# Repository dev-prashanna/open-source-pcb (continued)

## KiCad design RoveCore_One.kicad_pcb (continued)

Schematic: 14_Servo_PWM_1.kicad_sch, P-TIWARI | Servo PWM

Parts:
C60, C61: 100nF 16V; C_0603_1608Metric; MPN GRM188R71C104KA01D
J12: SERVO 1; PinHeader_1x03_P2.54mm_Vertical; MPN 61300311121
J13: SERVO 2; PinHeader_1x03_P2.54mm_Vertical; MPN 61300311121
J14: SERVO 3; PinHeader_1x03_P2.54mm_Vertical; MPN 61300311121
J15: SERVO 4; PinHeader_1x03_P2.54mm_Vertical; MPN 61300311121
R50, R52, R54, R56: 220; R_0603_1608Metric; MPN RC0603FR-07220RL
R51, R53, R55, R57: 100k; R_0603_1608Metric; MPN RC0603FR-07100KL
U19: PCA9685PW,118; TSSOP-28_4.4x9.7mm_P0.65mm; MPN PCA9685PW,118
U20: SN74AHCT1G125DBVR; SOT-23-5_Board; MPN SN74AHCT1G125DBVR

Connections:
+3V3: C60.1, U19.28 (VDD); also elsewhere on the board
BAT5: C61.1, U20.5 (VCC); also elsewhere on the board
GND: C60.2, C61.2, J12.1, J13.1, J14.1, J15.1, R51.2, R53.2, R55.2, R57.2, U19.1 (A0), U19.2 (A1), U19.3 (A2), U19.4 (A3), U19.5 (A4), U19.14 (VSS), U19.24 (A5), U19.25 (EXTCLK), U20.3 (GND); also elsewhere on the board
I2C_SCL: U19.26 (SCL); also elsewhere on the board
I2C_SDA: U19.27 (SDA); also elsewhere on the board
SERVO5: J12.2, J13.2, J14.2, J15.2; also elsewhere on the board
SERVO_OE: U19.23 (~OE), U20.1; also elsewhere on the board
SERVO_OUT0: J12.3, R50.2, R51.1
SERVO_OUT1: J13.3, R52.2, R53.1
SERVO_OUT2: J14.3, R54.2, R55.1
SERVO_OUT3: J15.3, R56.2, R57.1
SERVO_PWM0: U19.6 (LED0); also elsewhere on the board
SERVO_PWM1: U19.7 (LED1); also elsewhere on the board
SERVO_PWM2: U19.8 (LED2); also elsewhere on the board
SERVO_PWM3: U19.9 (LED3), U20.2
SERVO_SIG0: R50.1; also elsewhere on the board
SERVO_SIG1: R52.1; also elsewhere on the board
SERVO_SIG2: R54.1; also elsewhere on the board
SERVO_SIG3: R56.1, U20.4

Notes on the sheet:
PCA9685 0x40; default all-call 0x70, disable if conflicting extension is installed. GPIO15 high disables AHCT output buffers and PCA9685. Set low only after setting valid 50Hz pulses. Each servo: GND / servo rail / 5V PWM. Servo supply and BAT5 logic are distinct. Unused PWM channels intentionally 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

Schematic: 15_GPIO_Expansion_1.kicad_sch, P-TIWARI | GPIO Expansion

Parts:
C62: 100nF 16V; C_0603_1608Metric; MPN GRM188R71C104KA01D
J16: I2C 3V3; JST_GH_SM04B-GHS-TB_1x04-1MP_P1.25mm_Horizontal; MPN SM04B-GHS-TB(LF)(SN)
J17: SPI / LORA; JST_GH_SM06B-GHS-TB_1x06-1MP_P1.25mm_Horizontal; MPN SM06B-GHS-TB(LF)(SN)
J18: GPS / UART; JST_GH_SM04B-GHS-TB_1x04-1MP_P1.25mm_Horizontal; MPN SM04B-GHS-TB(LF)(SN)
J19: GPIO EXP 3V3; PinHeader_1x10_P2.00mm_Vertical; MPN M22-2011005
J20: ESP GPIO SHARED; PinHeader_1x10_P2.00mm_Vertical; MPN M22-2011005
J21: ESP GPIO INPUTS; PinHeader_1x08_P2.00mm_Vertical; MPN M22-2010805
TP1: EXP_B0; ServicePad_0.5mm; MPN PCB copper feature
TP2: EXP_B1; ServicePad_0.5mm; MPN PCB copper feature
TP3: EXP_B2; ServicePad_0.5mm; MPN PCB copper feature
U21: MCP23017-E/SS; SSOP-28_5.3x10.2mm_P0.65mm; MPN MCP23017-E/SS

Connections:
+3V3: C62.1, J16.1, J17.2, J18.2, J19.2, J20.2, U21.9 (V_{DD}); also elsewhere on the board
BAT_ADC: J20.8; also elsewhere on the board
BUZZ_PWM: J21.3; also elsewhere on the board
EN: U21.18 (~RESET); also elsewhere on the board
ENC_LA: J21.4; also elsewhere on the board
ENC_LB: J21.5; also elsewhere on the board
ENC_RA: J21.6; also elsewhere on the board
ENC_RB: J21.7; also elsewhere on the board
EXP_B0: TP1.1, U21.1 (GPB0)
EXP_B1: TP2.1, U21.2 (GPB1)
EXP_B2: TP3.1, U21.3 (GPB2)
EXP_B3: J19.6, U21.4 (GPB3)
EXP_B4: J19.7, U21.5 (GPB4)
EXP_B5: J19.8, U21.6 (GPB5)
EXP_B6: J19.9, U21.7 (GPB6)
EXP_B7: J19.10, U21.8 (GPB7); also elsewhere on the board
GND: C62.2, J16.2, J17.1, J18.1, J19.1, J19.3, J19.4, J19.5, J20.1, J21.1, U21.10 (V_{SS}), U21.15 (A0), U21.16 (A1), U21.17 (A2); also elsewhere on the board
I2C_SCL: J16.4, U21.12 (SCK); also elsewhere on the board
I2C_SDA: J16.3, U21.13 (SDA); also elsewhere on the board
IMU_INT: J20.7; also elsewhere on the board
M_A1: J20.3; also elsewhere on the board
M_A2: J20.4; also elsewhere on the board
M_B1: J20.5; also elsewhere on the board
M_B2: J20.6; also elsewhere on the board
M_FAULT: U21.22 (GPA1); also elsewhere on the board
M_SLEEP: U21.21 (GPA0); also elsewhere on the board
RGB_B: U21.28 (GPA7); also elsewhere on the board
RGB_G: U21.27 (GPA6); also elsewhere on the board
RGB_R: U21.26 (GPA5); also elsewhere on the board
SERVO_OE: J21.2; also elsewhere on the board
SPI_CS: J17.6, J21.8; also elsewhere on the board
SPI_MISO: J17.5; also elsewhere on the board
SPI_MOSI: J17.4; also elsewhere on the board
SPI_SCK: J17.3; also elsewhere on the board
TOF_INT: U21.24 (GPA3); also elsewhere on the board
TOF_XSHUT: U21.23 (GPA2); also elsewhere on the board
UART_RX: J18.4; also elsewhere on the board
UART_TX: J18.3; also elsewhere on the board
USER_BTN: U21.25 (GPA4); also elsewhere on the board
US_ECHO: J20.10; also elsewhere on the board
US_TRIG: J20.9; also elsewhere on the board

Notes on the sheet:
MCP23017 fixed 0x20. GPA0 sleep defaults LOW by external resistor; all pins reset as inputs. GPA2 must be open-drain emulated: output LOW for shutdown, input for release; never drive HIGH. GPB0..7 expansion are 3V3 GPIO; GPB7 also drives onboard load MOSFET. GPIO headers expose SHARED nets: disable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

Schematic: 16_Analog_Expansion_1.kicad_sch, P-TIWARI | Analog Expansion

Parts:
C63: 100nF 16V; C_0603_1608Metric; MPN GRM188R71C104KA01D
C64, C65, C66, C67: 10nF 25V; C_0603_1608Metric; MPN GRM188R71E103KA01D
D10, D11, D12, D13: BAT54S; SOT-23; MPN BAT54S-7-F
J22: ANALOG 0-3V3; JST_GH_SM06B-GHS-TB_1x06-1MP_P1.25mm_Horizontal; MPN SM06B-GHS-TB(LF)(SN)
R58, R59, R60, R61: 4.7k; R_0603_1608Metric; MPN RC0603FR-074K7L
U22: ADS1115IDGSR; TSSOP-10_3x3mm_P0.5mm; MPN ADS1115IDGSR

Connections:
+3V3: J22.1; also elsewhere on the board
+3V3_SENS: C63.1, D10.2 (K), D11.2 (K), D12.2 (K), D13.2 (K), U22.8 (VDD); also elsewhere on the board
AN0: C64.1, D10.3 (COM), R58.2, U22.4 (AIN0)
AN1: C65.1, D11.3 (COM), R59.2, U22.5 (AIN1)
AN2: C66.1, D12.3 (COM), R60.2, U22.6 (AIN2)
AN3: C67.1, D13.3 (COM), R61.2, U22.7 (AIN3)
AN_IN0: J22.3, R58.1
AN_IN1: J22.4, R59.1
AN_IN2: J22.5, R60.1
AN_IN3: J22.6, R61.1
GND: C63.2, C64.2, C65.2, C66.2, C67.2, D10.1 (A), D11.1 (A), D12.1 (A), D13.1 (A), J22.2, U22.1 (ADDR), U22.3 (GND); also elsewhere on the board
I2C_SCL: U22.10 (SCL); also elsewhere on the board
I2C_SDA: U22.9 (SDA); also elsewhere on the board

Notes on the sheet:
ADS1115 address 0x48, 860 samples/s aggregate maximum. Choose PGA +/-4.096V. Input voltage range remains 0..3.3V; PGA range is NOT input tolerance. 4.7k / 10nF filtering with Schottky clamps. Suitable for analog line sensor array. 4 channels sequentially sampled; high-speed line control may need an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

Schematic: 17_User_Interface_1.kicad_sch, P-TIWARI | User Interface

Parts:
BZ1: PKLCS1212E4001-R1; Buzzer_Murata_PKLCS1212E; MPN PKLCS1212E4001-R1
C68: 100nF 16V; C_0603_1608Metric; MPN GRM188R71C104KA01D
D4, D6: GREEN; LED_0603_1608Metric; MPN LTST-C190KGKT
D5: RED; LED_0603_1608Metric; MPN LTST-C190KRKT
D7: BLUE; LED_0603_1608Metric; MPN LTST-C193TBKT-5A
D8: SS34; D_SMA; MPN SS34
Q6, Q7: AO3400A; SOT-23; MPN AO3400A
R62: 10k; R_0603_1608Metric; MPN RC0603FR-0710KL
R63, R64, R65, R66, R69: 1k; R_0603_1608Metric; MPN RC0603FR-071KL
R67, R70: 100; R_0603_1608Metric; MPN RC0603FR-07100RL
R68, R71: 100k; R_0603_1608Metric; MPN RC0603FR-07100KL
SW3: SW3; SW_Push_1P1T-SH_NO_CK_KMR2xxG; MPN KMR221GLFS

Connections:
+3V3: BZ1.1 (+), R62.1, R63.1, R64.1, R65.1, R66.1, R69.1; also elsewhere on the board
BAT5: D8.1 (K); also elsewhere on the board
BUZZ_GATE: Q6.1 (G), R67.2, R68.1
BUZZ_LOW: BZ1.2 (-), Q6.3 (D), R69.2
BUZZ_PWM: R67.1; also elsewhere on the board
EXP_B7: R70.1; also elsewhere on the board
GND: C68.2, D4.1 (K), Q6.2 (S), Q7.2 (S), R68.2, R71.2, SW3.2; also elsewhere on the board
LED_B: D7.2 (A), R66.2
LED_G: D6.2 (A), R65.2
LED_R: D5.2 (A), R64.2
LOAD_GATE: Q7.1 (G), R70.2, R71.1
LOAD_LOW: D8.2 (A), Q7.3 (D); also elsewhere on the board
POWER_LED: D4.2 (A), R63.2
RGB_B: D7.1 (K); also elsewhere on the board
RGB_G: D6.1 (K); also elsewhere on the board
RGB_R: D5.1 (K); also elsewhere on the board
USER_BTN: C68.1, R62.2, SW3.1; also elsewhere on the board

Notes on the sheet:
R/G/B discrete programmable LEDs on expander GPA5..7; use green for Wi-Fi status. Piezo buzzer via GPIO2 MOSFET and discharge resistor. User button active LOW on GPA4. GPB7 load output 5V/250mA max, diode-protected for small inductive loads. BAT5 accessory budget shared. CAN: external 3V3 transceiv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

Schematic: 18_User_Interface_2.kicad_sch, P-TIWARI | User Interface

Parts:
J23: LOAD 5V 0.25A; JST_GH_SM02B-GHS-TB_1x02-1MP_P1.25mm_Horizontal; MPN SM02B-GHS-TB(LF)(SN)

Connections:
BAT5: J23.1; also elsewhere on the board
LOAD_LOW: J23.2; also elsewhere on the board

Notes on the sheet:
R/G/B discrete programmable LEDs on expander GPA5..7; use green for Wi-Fi status. Piezo buzzer via GPIO2 MOSFET and discharge resistor. User button active LOW on GPA4. GPB7 load output 5V/250mA max, diode-protected for small inductive loads. BAT5 accessory budget shared. CAN: external 3V3 transceiv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

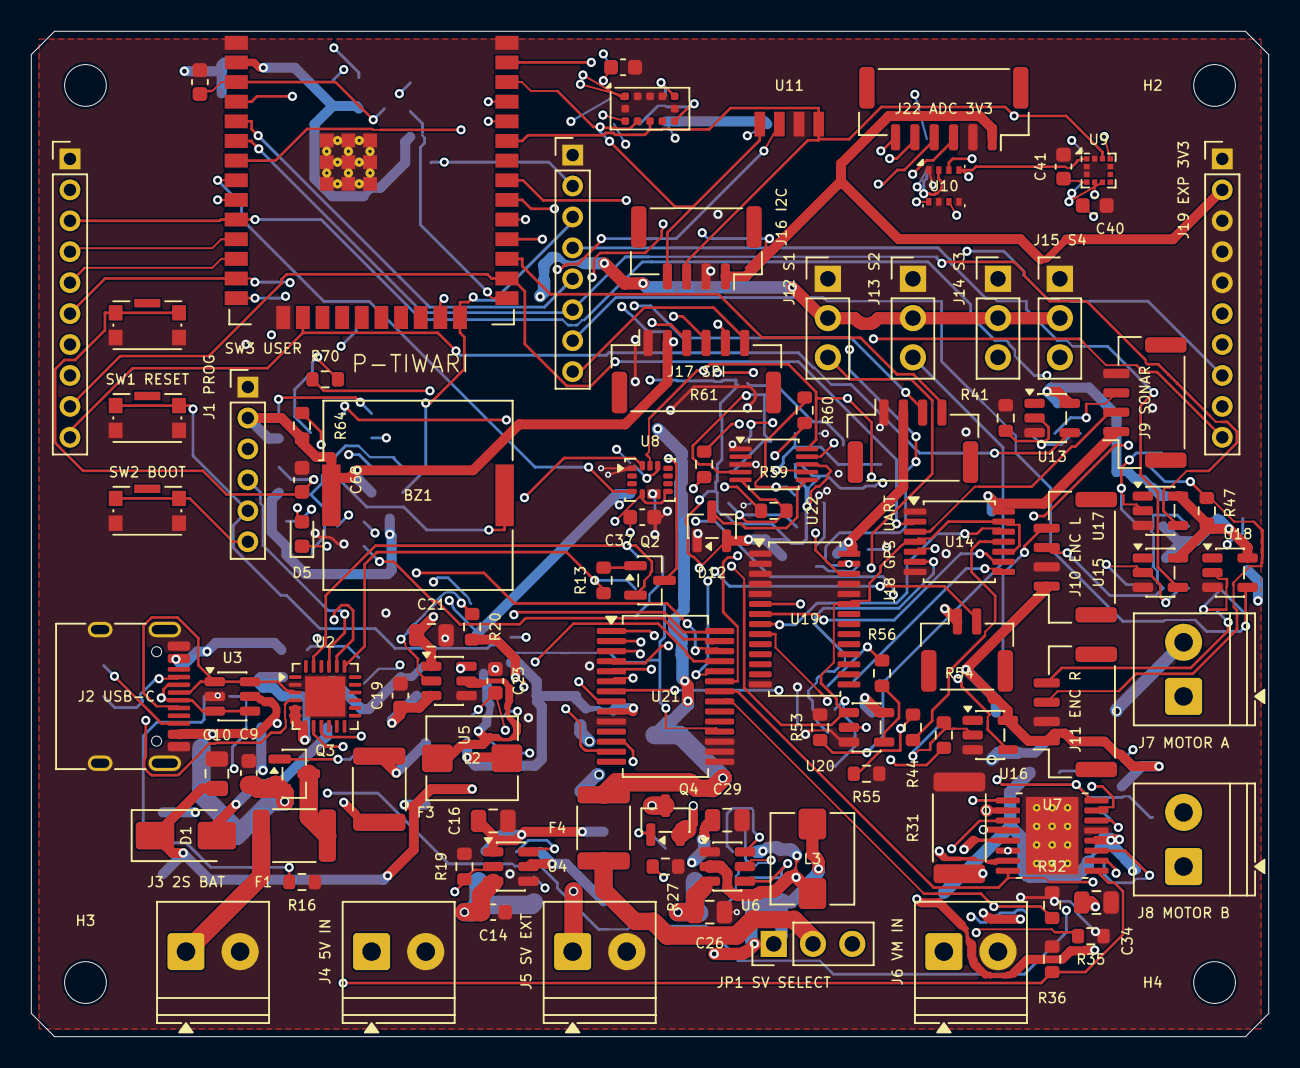
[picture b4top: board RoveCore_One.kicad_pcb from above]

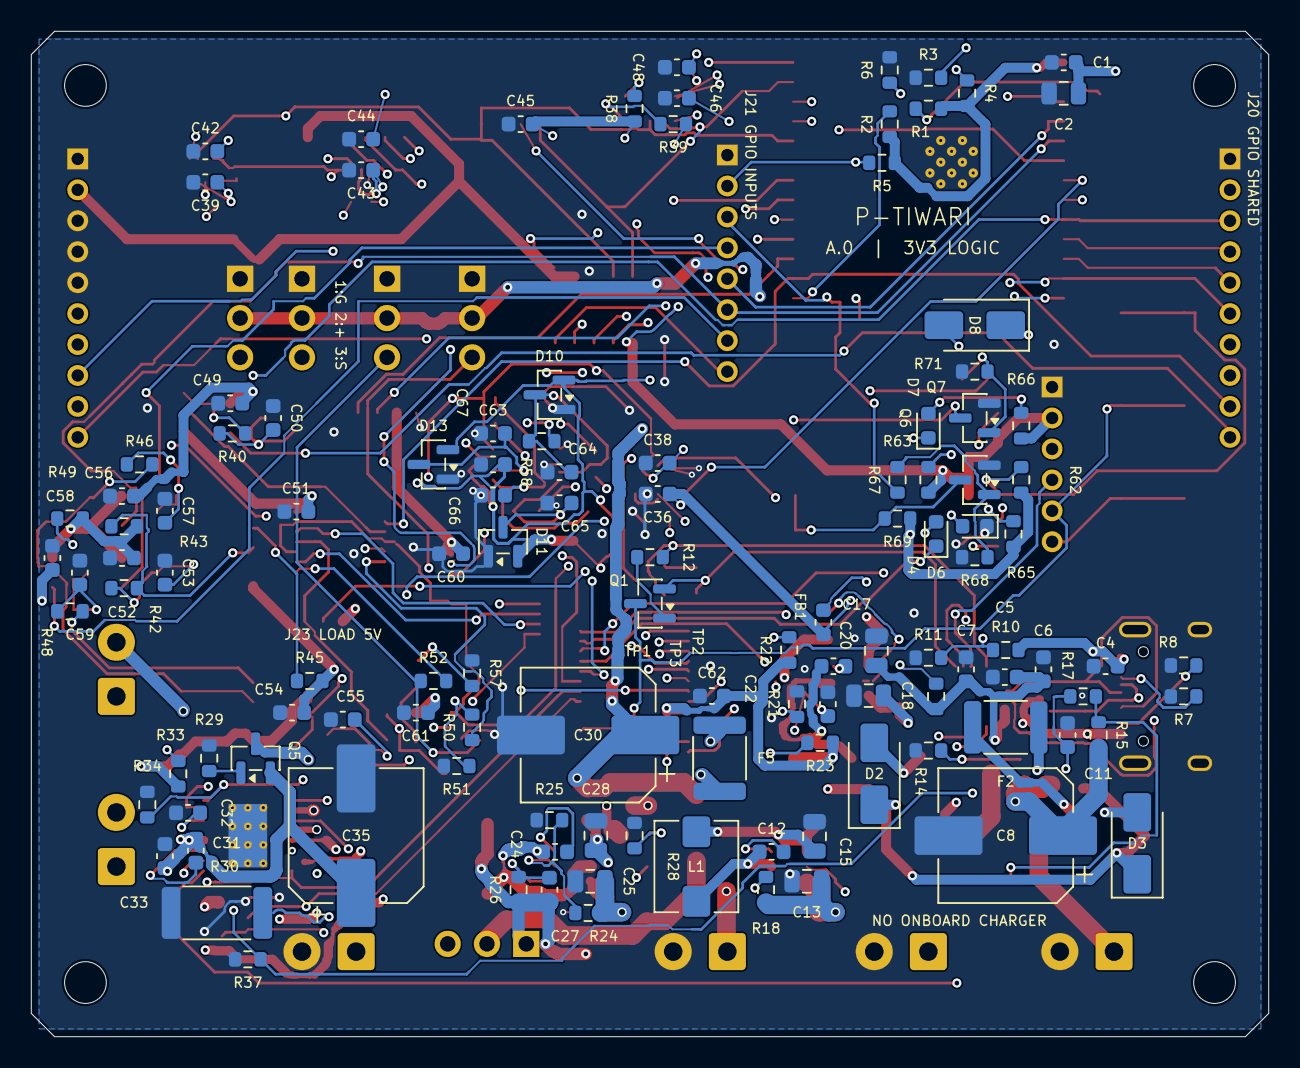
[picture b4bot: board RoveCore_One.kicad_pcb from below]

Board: 4 copper layers, 80.0 x 65.0 mm, 224 parts (122 on the bottom side), 135 nets.

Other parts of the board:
H1, H2, H3, H4: MountingHole_2.7mm_M2.5

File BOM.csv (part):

Reference,Value,MPN,Manufacturer,Footprint,Section,Datasheet
U1,ESP32-WROOM-32E-N8,ESP32-WROOM-32E-N8,Espressif,RoveCore:ESP32-WROOM-32E_Board,Controller,https://documentation.espressif.com/esp32-wroom-32e_esp32-wr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
C1,100nF 16V,GRM188R71C104KA01D,Murata,Capacitor_SMD:C_0603_1608Metric,Controller,
C2,22uF 10V,GRM21BR61A226ME44L,Murata,Capacitor_SMD:C_0805_2012Metric,Controller,
R1,10k,RC0603FR-0710KL,Yageo,Resistor_SMD:R_0603_1608Metric,Controller,
C3,1uF 16V,GRM188R61C105KA12D,Murata,Capacitor_SMD:C_0603_1608Metric,Controller,
R2,10k,RC0603FR-0710KL,Yageo,Resistor_SMD:R_0603_1608Metric,Controller,
R3,10k,RC0603FR-0710KL,Yageo,Resistor_SMD:R_0603_1608Metric,Controller,
R4,10k,RC0603FR-0710KL,Yageo,Resistor_SMD:R_0603_1608Metric,Controller,
R5,10k,RC0603FR-0710KL,Yageo,Resistor_SMD:R_0603_1608Metric,Controller,
R6,100k,RC0603FR-07100KL,Yageo,Resistor_SMD:R_0603_1608Metric,Controller,
SW1,SW1,KMR221GLFS,C&K,Button_Switch_SMD:SW_Push_1P1T-SH_NO_CK_KMR2xxG,Controller,
SW2,SW2,KMR221GLFS,C&K,Button_Switch_SMD:SW_Push_1P1T-SH_NO_CK_KMR2xxG,Controller,
J1,SERVICE 3V3,M22-2010605,Harwin,Connector_PinHeader_2.00mm:PinHeader_1x06_P2.00mm_Vertical,Controller,
J2,USB-C 5V DATA,TYPE-C-31-M-12,HRO,Connector_USB:USB_C_Receptacle_HRO_TYPE-C-31-M-12,USB Programming,
R7,5.1k,RC0603FR-075K1L,Yageo,Resistor_SMD:R_0603_1608Metric,USB Programming,
R8,5.1k,RC0603FR-075K1L,Yageo,Resistor_SMD:R_0603_1608Metric,USB Programming,
C4,1uF 16V,GRM188R61C105KA12D,Murata,Capacitor_SMD:C_0603_1608Metric,USB Programming,
U2,CP2102N-A02-GQFN24,CP2102N-A02-GQFN24,Silicon Labs,Package_DFN_QFN:QFN-24-1EP_4x4mm_P0.5mm_EP2.6x2.6mm,USB Programming,https://www.silabs.com/documents/public/data-sheets/cp2102n-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
C5,100nF 16V,GRM188R71C104KA01D,Murata,Capacitor_SMD:C_0603_1608Metric,USB Programming,
C6,100nF 16V,GRM188R71C104KA01D,Murata,Capacitor_SMD:C_0603_1608Metric,USB Programming,
C7,4.7uF 10V,GRM188R61A475KE15D,Murata,Capacitor_SMD:C_0603_1608Metric,USB Programming,
R9,1k,RC0603FR-071KL,Yageo,Resistor_SMD:R_0603_1608Metric,USB Programming,
R10,22.1k,RC0603FR-0722K1L,Yageo,Resistor_SMD:R_0603_1608Metric,USB Programming,
R11,47.5k,RC0603FR-0747K5L,Yageo,Resistor_SMD:R_0603_1608Metric,USB Programming,
U3,USBLC6-2SC6,USBLC6-2SC6,STMicroelectronics,Package_TO_SOT_SMD:SOT-23-6,USB Programming,
Q1,MMBT3904,MMBT3904,onsemi,Package_TO_SOT_SMD:SOT-23,USB Programming,
R12,10k,RC0603FR-0710KL,Yageo,Resistor_SMD:R_0603_1608Metric,USB Programming,
Q2,MMBT3904,MMBT3904,onsemi,Package_TO_SOT_SMD:SOT-23,USB Programming,
R13,10k,RC0603FR-0710KL,Yageo,Resistor_SMD:R_0603_1608Metric,USB Programming,
J3,2S BAT 6.4-8.4V,1984617,Phoenix Contact,"TerminalBlock_Phoenix:TerminalBlock_Phoenix_PT-1,5-2-3.5-H_1x02_P3.50mm_Horizontal",Power Inputs,
F1,2A hold,1812L200/16DR,Littelfuse,Fuse:Fuse_1812_4532Metric,Power Inputs,
Q3,AO3401A,AO3401A,Alpha & Omega Semiconductor,Package_TO_SOT_SMD:SOT-23,Power Inputs,https://www.aosmd.com/sites/default/files/res/datasheets/AO3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
R14,100k,RC0603FR-07100KL,Yageo,Resistor_SMD:R_0603_1608Metric,Power Inputs,
C8,470uF 16V,EEE-FK1C471P,Panasonic,Capacitor_SMD:CP_Elec_8x10.5,Power Inputs,
C9,100nF 16V,GRM188R71C104KA01D,Murata,Capacitor_SMD:C_0603_1608Metric,Power Inputs,
J4,EXT 5V LOGIC,1984617,Phoenix Contact,"TerminalBlock_Phoenix:TerminalBlock_Phoenix_PT-1,5-2-3.5-H_1x02_P3.50mm_Horizontal",Power Inputs,
F2,1.1A hold,1812L110/16DR,Littelfuse,Fuse:Fuse_1812_4532Metric,Power Inputs,
F3,0.5A hold,1812L050/24DR,Littelfuse,Fuse:Fuse_1812_4532Metric,Power Inputs,
D1,SS34,SS34,Diodes Inc.,Diode_SMD:D_SMA,Power Inputs,
D2,SS34,SS34,Diodes Inc.,Diode_SMD:D_SMA,Power Inputs,
D3,SS34,SS34,Diodes Inc.,Diode_SMD:D_SMA,Power Inputs,
C10,22uF 10V,GRM21BR61A226ME44L,Murata,Capacitor_SMD:C_0805_2012Metric,Power Inputs,
R15,100k,RC0603FR-07100KL,Yageo,Resistor_SMD:R_0603_1608Metric,Power Inputs,
R16,33k,RC0603FR-0733KL,Yageo,Resistor_SMD:R_0603_1608Metric,Power Inputs,
R17,1k,RC0603FR-071KL,Yageo,Resistor_SMD:R_0603_1608Metric,Power Inputs,
C11,100nF 16V,GRM188R71C104KA01D,Murata,Capacitor_SMD:C_0603_1608Metric,Power Inputs,
U4,AP63205WU-7,AP63205WU-7,Diodes Inc.,Package_TO_SOT_SMD:TSOT-23-6,Logic Regulators,https://www.diodes.com/datasheet/download/AP63200-AP63201-AP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
R18,100k,RC0603FR-07100KL,Yageo,Resistor_SMD:R_0603_1608Metric,Logic Regulators,
R19,27.4k,RC0603FR-0727K4L,Yageo,Resistor_SMD:R_0603_1608Metric,Logic Regulators,
C12,100nF 16V,GRM188R71C104KA01D,Murata,Capacitor_SMD:C_0603_1608Metric,Logic Regulators,
C13,10uF 16V,GRM21BR61C106KE15L,Murata,Capacitor_SMD:C_0805_2012Metric,Logic Regulators,
C14,100nF 16V,GRM188R71C104KA01D,Murata,Capacitor_SMD:C_0603_1608Metric,Logic Regulators,
L1,4.7uH,SRP5030T-4R7M,Bourns,Inductor_SMD:L_Bourns_SRP5030T,Logic Regulators,
C15,22uF 10V,GRM21BR61A226ME44L,Murata,Capacitor_SMD:C_0805_2012Metric,Logic Regulators,
C16,22uF 10V,GRM21BR61A226ME44L,Murata,Capacitor_SMD:C_0805_2012Metric,Logic Regulators,
U5,AP63203WU-7,AP63203WU-7,Diodes Inc.,Package_TO_SOT_SMD:TSOT-23-6,Logic Regulators,https://www.diodes.com/datasheet/download/AP63200-AP63201-AP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
R20,100k,RC0603FR-07100KL,Yageo,Resistor_SMD:R_0603_1608Metric,Logic Regulators,
R21,100k,RC0603FR-07100KL,Yageo,Resistor_SMD:R_0603_1608Metric,Logic Regulators,
C17,100nF 16V,GRM188R71C104KA01D,Murata,Capacitor_SMD:C_0603_1608Metric,Logic Regulators,
C18,10uF 16V,GRM21BR61C106KE15L,Murata,Capacitor_SMD:C_0805_2012Metric,Logic Regulators,
C19,100nF 16V,GRM188R71C104KA01D,Murata,Capacitor_SMD:C_0603_1608Metric,Logic Regulators,
L2,4.7uH,SRP5030T-4R7M,Bourns,Inductor_SMD:L_Bourns_SRP5030T,Logic Regulators,
C20,22uF 10V,GRM21BR61A226ME44L,Murata,Capacitor_SMD:C_0805_2012Metric,Logic Regulators,
C21,22uF 10V,GRM21BR61A226ME44L,Murata,Capacitor_SMD:C_0805_2012Metric,Logic Regulators,
FB1,600R @100MHz,BLM18AG601SN1D,Murata,Inductor_SMD:L_0603_1608Metric,Logic Regulators,
C22,4.7uF 10V,GRM188R61A475KE15D,Murata,Capacitor_SMD:C_0603_1608Metric,Logic Regulators,
C23,100nF 16V,GRM188R71C104KA01D,Murata,Capacitor_SMD:C_0603_1608Metric,Logic Regulators,
R22,2.2k,RC0603FR-072K2L,Yageo,Resistor_SMD:R_0603_1608Metric,Logic Regulators,
R23,2.2k,RC0603FR-072K2L,Yageo,Resistor_SMD:R_0603_1608Metric,Logic Regulators,
U6,TPS54302DDCR,TPS54302DDCR,Texas Instruments,Package_TO_SOT_SMD:SOT-23-6,Servo Power,https://www.ti.com/lit/ds/symlink/tps54302.pdf
R24,100k,RC0603FR-07100KL,Yageo,Resistor_SMD:R_0603_1608Metric,Servo Power,
R25,27.4k,RC0603FR-0727K4L,Yageo,Resistor_SMD:R_0603_1608Metric,Servo Power,
C24,100nF 16V,GRM188R71C104KA01D,Murata,Capacitor_SMD:C_0603_1608Metric,Servo Power,
C25,10uF 16V,GRM21BR61C106KE15L,Murata,Capacitor_SMD:C_0805_2012Metric,Servo Power,
C26,10uF 16V,GRM21BR61C106KE15L,Murata,Capacitor_SMD:C_0805_2012Metric,Servo Power,
L3,10uH,SRP5030T-100M,Bourns,Inductor_SMD:L_Bourns_SRP5030T,Servo Power,
R26,100k,RC0603FR-07100KL,Yageo,Resistor_SMD:R_0603_1608Metric,Servo Power,
R27,13.3k,RC0603FR-0713K3L,Yageo,Resistor_SMD:R_0603_1608Metric,Servo Power,
C27,75pF 50V,GRM1885C1H750JA01D,Murata,Capacitor_SMD:C_0603_1608Metric,Servo Power,
C28,22uF 10V,GRM21BR61A226ME44L,Murata,Capacitor_SMD:C_0805_2012Metric,Servo Power,
C29,22uF 10V,GRM21BR61A226ME44L,Murata,Capacitor_SMD:C_0805_2012Metric,Servo Power,
J5,SERVO EXT 5-6V,1984617,Phoenix Contact,"TerminalBlock_Phoenix:TerminalBlock_Phoenix_PT-1,5-2-3.5-H_1x02_P3.50mm_Horizontal",Servo Power,
Q4,AO3401A,AO3401A,Alpha & Omega Semiconductor,Package_TO_SOT_SMD:SOT-23,Servo Power,https://www.aosmd.com/sites/default/files/res/datasheets/AO3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
R28,100k,RC0603FR-07100KL,Yageo,Resistor_SMD:R_0603_1608Metric,Servo Power,
JP1,SERVO SELECT 1-2 BAT / 2-3 EXT,61300311121,Wurth Elektronik,Connector_PinHeader_2.54mm:PinHeader_1x03_P2.54mm_Vertical,Servo Power,
F4,2A hold,1812L200/16DR,Littelfuse,Fuse:Fuse_1812_4532Metric,Servo Power,
C30,470uF 16V,EEE-FK1C471P,Panasonic,Capacitor_SMD:CP_Elec_8x10.5,Servo Power,
J6,VM 3-8.4V,1984617,Phoenix Contact,"TerminalBlock_Phoenix:TerminalBlock_Phoenix_PT-1,5-2-3.5-H_1x02_P3.50mm_Horizontal",Motor Driver,
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
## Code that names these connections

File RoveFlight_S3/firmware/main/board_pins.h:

// Generated from verified GPIO_Allocation.csv. RF-S3-A0 / N8R2 only.
#pragma once
#define PIN_BOOT 0
#define PIN_CURRENT_ADC 1
#define PIN_BAT_ADC 2
#define PIN_PWM_M1 4
#define PIN_PWM_M2 5
#define PIN_PWM_M3 6
#define PIN_PWM_M4 7
#define PIN_I2C_SDA 8
#define PIN_IMU_INT 9
#define PIN_IMU_CS 10
#define PIN_SPI_MOSI 11
#define PIN_SPI_SCK 12
#define PIN_SPI_MISO 13
#define PIN_BARO_CS 14
#define PIN_IR_RX 15
#define PIN_TOF_INT 16
#define PIN_TOF_XSHUT 17
#define PIN_I2C_SCL 18
#define PIN_USB_DM 19
#define PIN_USB_DP 20
#define PIN_STATUS_LED 21
#define PIN_ARM_CLK 38
#define PIN_WD_HEARTBEAT 39
#define PIN_KILL_OD 40
#define PIN_RC_RX 41
#define PIN_RC_TX 42
#define PIN_DEBUG_TX 43
#define PIN_DEBUG_RX 44
#define PIN_FLOW_CS 47
#define PIN_FLOW_INT 48

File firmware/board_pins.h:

// P-TIWARI A.0; pin contract only, not validated application firmware.
#pragma once
namespace p_tiwari {
constexpr int PIN_BOOT = 0;
constexpr int PIN_U0_TX = 1;
constexpr int PIN_BUZZ_PWM = 2;
constexpr int PIN_U0_RX = 3;
constexpr int PIN_US_TRIG = 4;
constexpr int PIN_SPI_CS = 5;
constexpr int PIN_STRAP12 = 12;
constexpr int PIN_US_ECHO = 13;
constexpr int PIN_M_B2 = 14;
constexpr int PIN_SERVO_OE = 15;
constexpr int PIN_UART_RX = 16;
constexpr int PIN_UART_TX = 17;
constexpr int PIN_SPI_SCK = 18;
constexpr int PIN_SPI_MISO = 19;
constexpr int PIN_I2C_SDA = 21;
constexpr int PIN_I2C_SCL = 22;
constexpr int PIN_SPI_MOSI = 23;
constexpr int PIN_M_A1 = 25;
constexpr int PIN_M_A2 = 26;
constexpr int PIN_M_B1 = 27;
constexpr int PIN_IMU_INT = 32;
constexpr int PIN_BAT_ADC = 33;
constexpr int PIN_ENC_RA = 34;
constexpr int PIN_ENC_RB = 35;
constexpr int PIN_ENC_LA = 36;
constexpr int PIN_ENC_LB = 39;
constexpr unsigned IMU_ADDR=0x6A, MAG_ADDR=0x1C, BME_ADDR=0x76, ALS_ADDR=0x10;
constexpr unsigned TOF_ADDR=0x29, PWM_ADDR=0x40, EXP_ADDR=0x20, ADC_ADDR=0x48;
}

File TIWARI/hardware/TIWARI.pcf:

# Physical SG48 pin numbers; generated pin parity is checked against design.json.
set_io clk_12m 35
set_io reset_n 10
set_io uart_rx 9
set_io uart_tx 6
set_io user_led 11
set_io fault_led 12
set_io pwm[0] 13
set_io pwm[1] 18
set_io gpio[0] 2
set_io gpio[1] 3
set_io gpio[2] 4
set_io gpio[3] 44
set_io gpio[4] 45
set_io gpio[5] 46
set_io gpio[6] 47
set_io gpio[7] 48
set_io gpio[8] 23
set_io gpio[9] 25
set_io gpio[10] 26
set_io gpio[11] 27
set_io gpio[12] 28
set_io gpio[13] 31
set_io gpio[14] 32
set_io gpio[15] 34

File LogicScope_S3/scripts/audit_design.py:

"""Independent manifest/XML/PCB pin checks and ground-return geometry audit."""
from route_utils import *
import xml.etree.ElementTree as ET
from collections import defaultdict
from shapely.ops import unary_union
parts=json.loads((ROOT/'design.json').read_text());manifest={(c['ref'],pin):net for c in parts for pin,net in c['nets'].items()};xml=ET.parse(ROOT/'reports/LogicScope_S3.xml').getroot();actual={}
for net in xml.find('nets'):
 for q in net.findall('node'):actual[(q.attrib['ref'],q.attrib['pin'])]=net.attrib['name'].lstrip('/')
errors=[]
for (ref,num),net in manifest.items():
 pads=[q for q in fps[ref].Pads() if q.GetNumber()==num]
 if not pads:errors.append([ref,num,'missing pad'])
 for q in pads:
  if net is None:
   if q.GetNetname() and not q.GetNetname().startswith('unconnected-'):errors.append([ref,num,'unexpected connected NC',q.GetNetname()])
  elif actual.get((ref,num))!=net or q.GetNetname()!=net:errors.append([ref,num,net,actual.get((ref,num)),q.GetNetname()])
for key,net in actual.items():
 if not key[0].startswith('#') and key not in manifest and not net.startswith('unconnected-'):errors.append(['unexpected pin',key,net])
def nn(ref,num):return actual.get((ref,str(num)))
checks={
 'manifest_schematic_and_pcb_match':not errors,
 'eight_parallel_bits':all(nn('U1',4+i)==nn('U2',18-i)==f'D{i}' for i in range(8)),
 'input_protection_each_channel':all(nn('R'+str(10+i),1)==f'CH{i}' and nn('R'+str(10+i),2)==nn('U2',2+i)==f'IN{i}' for i in range(8)),
 'pulldowns_each_input':all(nn('R'+str(20+i),1)==f'IN{i}' and nn('R'+str(20+i),2)=='GND' for i in range(8)),
 'buffer_direction_and_supply':nn('U2',1)==nn('U2',20)=='+3V3' and nn('U2',10)=='GND' and nn('U2',19)=='BUF_OE_N',
 'usb_native_gpio19_20':nn('U1',13)=='USB_DM' and nn('U1',14)=='USB_DP',
 'usb_dual_data_pads':nn('J3','A6')==nn('J3','B6')=='USB_DP_CONN' and nn('J3','A7')==nn('J3','B7')=='USB_DM_CONN',
 'usb_cc_separate':nn('J3','A5')==nn('R30',1)=='USB_CC1' and nn('J3','B5')==nn('R31',1)=='USB_CC2' and nn('R30',2)==nn('R31',2)=='GND',
 'buck_pin_map':all(nn('U3',pin)==net for pin,net in [(1,'+3V3'),(2,'VUSB'),(3,'VUSB'),(4,'GND'),(5,'SW'),(6,'BST')]),
 'hardware_clock_loopback':nn('U1',20)==nn('R4',1)=='SAMPLE_CLK' and nn('R4',2)==nn('U1',19)=='CAM_PCLK',
 'no_external_5V_direct_to_mcu':not any(q.GetNetname() in {'USB_5V','VUSB'} or q.GetNetname().startswith('CH') for q in fps['U1'].Pads()),
 'two_copper_layers':b.GetCopperLayerCount()==2,
 'optional_esd_dnp':all(bool(fps[ref].GetAttributes()&p.FP_DNP) for ref in ['U5','U6']),
 'etched_and_silk_tiwari':all(any(isinstance(q,p.PCB_TEXT) and q.GetText()=='TIWARI' and q.GetLayer()==layer for q in b.GetDrawings()) for layer in [p.F_Cu,p.F_SilkS]),
}
for ref,nets in [('J1',['CH0','GND','CH1','GND','CH2','GND','CH3','GND','CH4','GND']),('J2',['CH5','GND','CH6','GND','CH7','GND','VREF_3V3','GND',None,None])]:
 checks[ref+'_pinout']=all(nn(ref,i+1)==net if net else nn(ref,i+1).startswith('unconnected-') for i,net in enumerate(nets))
connectivity={'checks':checks,'errors':errors,'electrical_parts':len(parts),'all_passed':all(checks.values())}
(ROOT/'reports/Connectivity_Audit.json').write_text(json.dumps(connectivity,indent=2)+'\n')

def filled(z):
 ps=z.GetFilledPolysList(z.GetLayer())
 def ring(r):return [(p.ToMM(r.CPoint(k).x),p.ToMM(r.CPoint(k).y)) for k in range(r.PointCount())]
 return [Polygon(ring(ps.COutline(i)),[ring(ps.CHole(i,j)) for j in range(ps.HoleCount(i))]).buffer(0) for i in range(ps.OutlineCount())]
rear_zones=[z for z in b.Zones() if not z.GetIsRuleArea() and z.GetLayer()==p.B_Cu and z.GetNetname()=='GND']
rear_polys=[g for z in rear_zones for g in filled(z)];rear=unary_union(rear_polys)
netstats=defaultdict(lambda:{'length_mm':0.,'rear_length_mm':0.,'vias':0,'widths_mm':set(),'layers':set()});critical_errors=[];plane_gaps=[];via_pad=[]
for tr in b.GetTracks():
 net=tr.GetNetname();e=netstats[net]
 if isinstance(tr,p.PCB_VIA):
  e['vias']+=1;hole=Point(*xy(tr)).buffer(p.ToMM(tr.GetDrill())/2)
  if any(hole.intersects(g) for l in layers for g in smd[l]):via_pad.append({'net':net,'xy':xy(tr)})
  continue
 a,z=tr.GetStart(),tr.GetEnd();path=LineString([(p.ToMM(a.x),p.ToMM(a.y)),(p.ToMM(z.x),p.ToMM(z.y))]);length=p.ToMM(tr.GetLength());e['length_mm']+=length;e['widths_mm'].add(round(p.ToMM(tr.GetWidth()),4));e['layers'].add(b.GetLayerName(tr.GetLayer()))
 if tr.GetLayer()==p.B_Cu:e['rear_length_mm']+=length
 if net in {f'D{i}' for i in range(8)} or net.startswith('USB_D'):
  if tr.GetLayer()!=p.F_Cu:critical_errors.append(net)
  if not rear.buffer(.01).covers(path):plane_gaps.append({'net':net,'length_missing_mm':path.difference(rear.buffer(.01)).length})
for e in netstats.values():
 for key in ['length_mm','rear_length_mm']:e[key]=round(e[key],4)
 for key in ['layers','widths_mm']:e[key]=sorted(e[key])
critical_vias={n:e['vias'] for n,e in netstats.items() if (n.startswith('USB_D') or n in {f'D{i}' for i in range(8)}) and e['vias']}
antenna=[]
for fp in b.GetFootprints():
 for zone in fp.Zones():
  if not zone.GetIsRuleArea():continue
  ps=zone.Outline()
  for i in range(ps.OutlineCount()):
   r=ps.COutline(i);g=Polygon([(p.ToMM(r.CPoint(k).x),p.ToMM(r.CPoint(k).y)) for k in range(r.PointCount())])
   for l in layers:
    if any(g.intersection(s).area>1e-5 for s,n in zip(geoms[l],owners[l]) if n!='__KEEP_OUT'):antenna.append('copper overlap')
   if g.intersection(rear).area>1e-5:antenna.append('rear fill overlap')
physical={'copper_layers':b.GetCopperLayerCount(),'board_mm':[55,40],'nominal_thickness_mm':p.ToMM(b.GetDesignSettings().GetBoardThickness()),'footprints':len(fps),'rear_ground_polygons':len(rear_polys),'rear_ground_area_mm2':round(rear.area,3),'rear_coverage_of_2200mm2_percent':round(100*rear.area/2200,2),'critical_routes_on_wrong_layer':critical_errors,'critical_vias':critical_vias,'critical_centerline_reference_gaps':plane_gaps,'antenna_copper_errors':antenna,'board_via_drills_in_smd_lands':via_pad,'nets':dict(netstats),'performance_validation':'UNMEASURED; finite capture target 1 MS/s, no released continuous rate'}
physical['all_passed']=len(rear_polys)==1 and not any([critical_errors,critical_vias,plane_gaps,antenna,via_pad])
(ROOT/'reports/Physical_Audit.json').write_text(json.dumps(physical,indent=2)+'\n')
with (ROOT/'Placement.csv').open('w') as f:
 w=csv.writer(f);w.writerow(['Reference','Value','X_mm','Y_mm','Rotation_deg','Side','DNP'])
 for ref,fp in sorted(fps.items()):w.writerow([ref,fp.GetValue(),*xy(fp),fp.GetOrientationDegrees(),'F' if fp.GetLayer()==p.F_Cu else 'B','YES' if fp.GetAttributes()&p.FP_DNP else 'NO'])
print('Connectivity checks',checks,'errors',errors)
print('Physical audit:',{k:v for k,v in physical.items() if k!='nets'})
if not connectivity['all_passed'] or not physical['all_passed']:raise SystemExit(1)

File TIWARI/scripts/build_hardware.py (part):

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 '16':'FLASH_SCK','17':'FLASH_MOSI','18':'FLASH_MISO','21':'FLASH_CS_N','23':'CDONE','24':'CRESET_N',
 '38':'UART_TO_CPU','39':'UART_FROM_CPU','61':'EE_DATA','62':'EE_CLK','63':'EE_CS'})
add('U2','Interface_USB','FT2232HL','FT2232HL-REEL',ft,(12.5,18),source=FTDI)
add('Y1','Device','Crystal_GND24','12MHz',{'1':'XTAL_IN','2':'GND','3':'XTAL_OUT','4':'GND'},(12.5,9),'Crystal:Crystal_SMD_3225-4Pin_3.2x2.5mm',mpn='ABM8-12.000MHZ-B2-T')
c('27p','XTAL_IN','GND',(10,9),90);c('27p','XTAL_OUT','GND',(15,9),90)
r('12k','FT_REF','GND',(6,15),90);r('10k','+3V3','FT_RESET_N',(6,11),90);c('100n','FT_RESET_N','GND',(8,11),90)
add('FB1','Device','FerriteBead','600R@100MHz',{'1':'+3V3','2':'FT_VPHY'},(6,18),'Inductor_SMD:L_0603_1608Metric',rot=90,mpn='BLM18AG601SN1D')
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fp.update({str(pin):'D'+str(i) for i,pin in enumerate(gpio_pins)})
add('U1','TIWARI','ICE40UP5K-SG48ITR_REVIEWED','ICE40UP5K-SG48ITR',fp,(34,18),fp='TIWARI:UP5K_SG48_Reviewed',source=FPGA)
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add('Y2','Oscillator','ASE-xxxMHz','12MHz 3V3 CMOS',{'1':'+3V3','2':'GND','3':'CLK12','4':'+3V3'},(28,8),'Oscillator:Oscillator_SMD_Abracon_ASE-4Pin_3.2x2.5mm',mpn='ASE-12.000MHZ-LC-T',source='https://abracon.com/Oscillators/ASE.pdf')
c('100n','+3V3','GND',(28,5.5))
r('10k','+3V3','FLASH_WP_N',(26,28));r('10k','+3V3','FLASH_HOLD_N',(29,28))
r('100','+1V2','FPGA_PLL',(34,23.5));c('1u','FPGA_PLL','GND',(36,23.5))
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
